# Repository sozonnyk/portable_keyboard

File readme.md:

## DIY Keyboard

This one is WIP

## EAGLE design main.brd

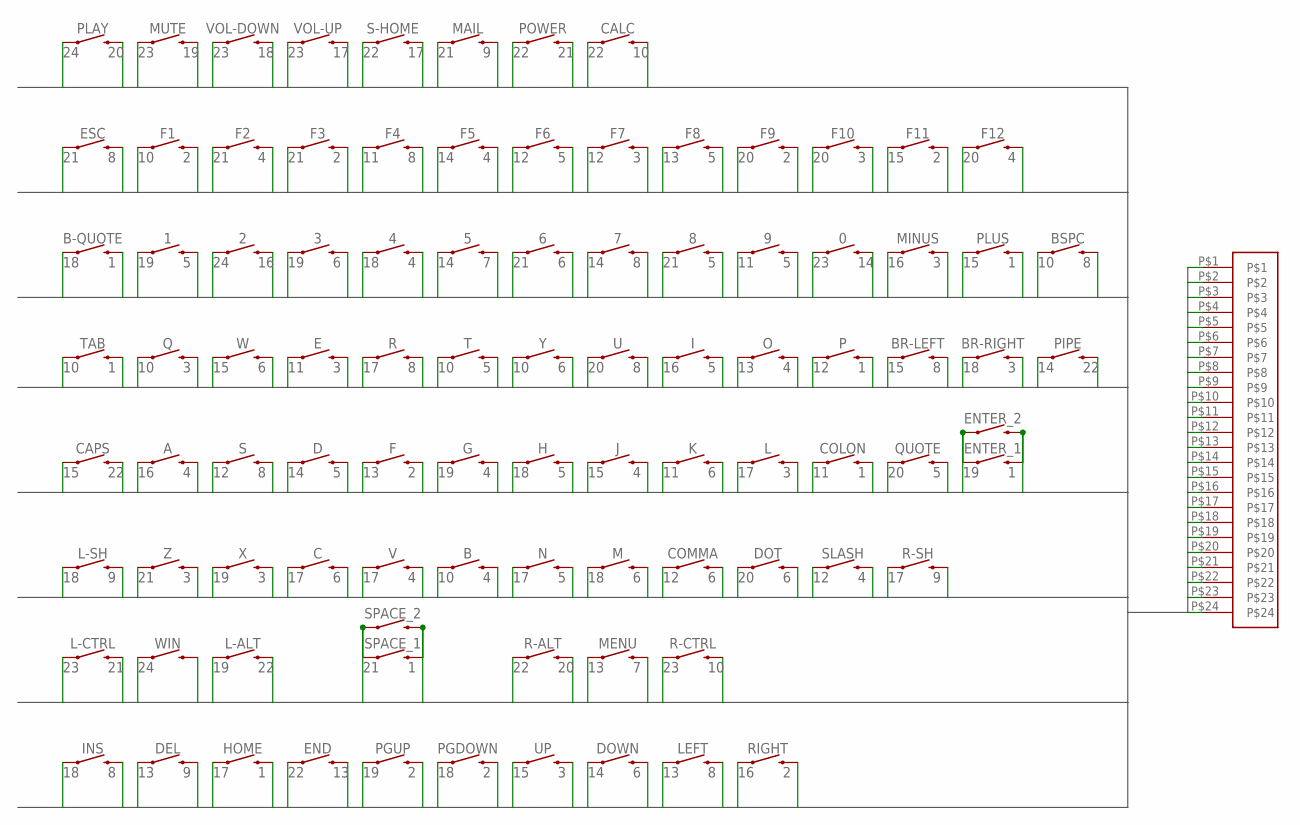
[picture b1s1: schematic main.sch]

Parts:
0, 1, 2, 3, 4, 5, 6, 7, 8, 9: MOMENTARY-SWITCH-SPST-SMD-5.2MM-TALL; TACTILE_SWITCH_SMD_5.2MM
A: MOMENTARY-SWITCH-SPST-SMD-5.2MM-TALL; TACTILE_SWITCH_SMD_5.2MM
B: MOMENTARY-SWITCH-SPST-SMD-5.2MM-TALL; TACTILE_SWITCH_SMD_5.2MM
B-QUOTE: MOMENTARY-SWITCH-SPST-SMD-5.2MM-TALL; TACTILE_SWITCH_SMD_5.2MM
BR-LEFT: MOMENTARY-SWITCH-SPST-SMD-5.2MM-TALL; TACTILE_SWITCH_SMD_5.2MM
BR-RIGHT: MOMENTARY-SWITCH-SPST-SMD-5.2MM-TALL; TACTILE_SWITCH_SMD_5.2MM
BSPC: MOMENTARY-SWITCH-SPST-SMD-5.2MM-TALL; TACTILE_SWITCH_SMD_5.2MM
C: MOMENTARY-SWITCH-SPST-SMD-5.2MM-TALL; TACTILE_SWITCH_SMD_5.2MM
CALC: MOMENTARY-SWITCH-SPST-SMD-5.2MM-TALL; TACTILE_SWITCH_SMD_5.2MM
CAPS: MOMENTARY-SWITCH-SPST-SMD-5.2MM-TALL; TACTILE_SWITCH_SMD_5.2MM
COLON: MOMENTARY-SWITCH-SPST-SMD-5.2MM-TALL; TACTILE_SWITCH_SMD_5.2MM
COMMA: MOMENTARY-SWITCH-SPST-SMD-5.2MM-TALL; TACTILE_SWITCH_SMD_5.2MM
D: MOMENTARY-SWITCH-SPST-SMD-5.2MM-TALL; TACTILE_SWITCH_SMD_5.2MM
DEL: MOMENTARY-SWITCH-SPST-SMD-5.2MM-TALL; TACTILE_SWITCH_SMD_5.2MM
DOT: MOMENTARY-SWITCH-SPST-SMD-5.2MM-TALL; TACTILE_SWITCH_SMD_5.2MM
DOWN: MOMENTARY-SWITCH-SPST-SMD-5.2MM-TALL; TACTILE_SWITCH_SMD_5.2MM
E: MOMENTARY-SWITCH-SPST-SMD-5.2MM-TALL; TACTILE_SWITCH_SMD_5.2MM
END: MOMENTARY-SWITCH-SPST-SMD-5.2MM-TALL; TACTILE_SWITCH_SMD_5.2MM
ENTER_1, ENTER_2: MOMENTARY-SWITCH-SPST-SMD-5.2MM-TALL; TACTILE_SWITCH_SMD_5.2MM
ESC: MOMENTARY-SWITCH-SPST-SMD-5.2MM-TALL; TACTILE_SWITCH_SMD_5.2MM
F, F1, F2, F3, F4, F5, F6, F7, F8, F9, F10, F11, F12: MOMENTARY-SWITCH-SPST-SMD-5.2MM-TALL; TACTILE_SWITCH_SMD_5.2MM
G: MOMENTARY-SWITCH-SPST-SMD-5.2MM-TALL; TACTILE_SWITCH_SMD_5.2MM
H: MOMENTARY-SWITCH-SPST-SMD-5.2MM-TALL; TACTILE_SWITCH_SMD_5.2MM
HOME: MOMENTARY-SWITCH-SPST-SMD-5.2MM-TALL; TACTILE_SWITCH_SMD_5.2MM
I: MOMENTARY-SWITCH-SPST-SMD-5.2MM-TALL; TACTILE_SWITCH_SMD_5.2MM
INS: MOMENTARY-SWITCH-SPST-SMD-5.2MM-TALL; TACTILE_SWITCH_SMD_5.2MM
J: MOMENTARY-SWITCH-SPST-SMD-5.2MM-TALL; TACTILE_SWITCH_SMD_5.2MM
K: MOMENTARY-SWITCH-SPST-SMD-5.2MM-TALL; TACTILE_SWITCH_SMD_5.2MM
L: MOMENTARY-SWITCH-SPST-SMD-5.2MM-TALL; TACTILE_SWITCH_SMD_5.2MM
L-ALT: MOMENTARY-SWITCH-SPST-SMD-5.2MM-TALL; TACTILE_SWITCH_SMD_5.2MM
L-CTRL: MOMENTARY-SWITCH-SPST-SMD-5.2MM-TALL; TACTILE_SWITCH_SMD_5.2MM
L-SH: MOMENTARY-SWITCH-SPST-SMD-5.2MM-TALL; TACTILE_SWITCH_SMD_5.2MM
LEFT: MOMENTARY-SWITCH-SPST-SMD-5.2MM-TALL; TACTILE_SWITCH_SMD_5.2MM
M: MOMENTARY-SWITCH-SPST-SMD-5.2MM-TALL; TACTILE_SWITCH_SMD_5.2MM
MAIL: MOMENTARY-SWITCH-SPST-SMD-5.2MM-TALL; TACTILE_SWITCH_SMD_5.2MM
MENU: MOMENTARY-SWITCH-SPST-SMD-5.2MM-TALL; TACTILE_SWITCH_SMD_5.2MM
MINUS: MOMENTARY-SWITCH-SPST-SMD-5.2MM-TALL; TACTILE_SWITCH_SMD_5.2MM
MUTE: MOMENTARY-SWITCH-SPST-SMD-5.2MM-TALL; TACTILE_SWITCH_SMD_5.2MM
N: MOMENTARY-SWITCH-SPST-SMD-5.2MM-TALL; TACTILE_SWITCH_SMD_5.2MM
O: MOMENTARY-SWITCH-SPST-SMD-5.2MM-TALL; TACTILE_SWITCH_SMD_5.2MM
P: MOMENTARY-SWITCH-SPST-SMD-5.2MM-TALL; TACTILE_SWITCH_SMD_5.2MM
PGDOWN: MOMENTARY-SWITCH-SPST-SMD-5.2MM-TALL; TACTILE_SWITCH_SMD_5.2MM
PGUP: MOMENTARY-SWITCH-SPST-SMD-5.2MM-TALL; TACTILE_SWITCH_SMD_5.2MM
PIPE: MOMENTARY-SWITCH-SPST-SMD-5.2MM-TALL; TACTILE_SWITCH_SMD_5.2MM
PLAY: MOMENTARY-SWITCH-SPST-SMD-5.2MM-TALL; TACTILE_SWITCH_SMD_5.2MM
PLUS: MOMENTARY-SWITCH-SPST-SMD-5.2MM-TALL; TACTILE_SWITCH_SMD_5.2MM
POWER: MOMENTARY-SWITCH-SPST-SMD-5.2MM-TALL; TACTILE_SWITCH_SMD_5.2MM
Q: MOMENTARY-SWITCH-SPST-SMD-5.2MM-TALL; TACTILE_SWITCH_SMD_5.2MM
QUOTE: MOMENTARY-SWITCH-SPST-SMD-5.2MM-TALL; TACTILE_SWITCH_SMD_5.2MM
R: MOMENTARY-SWITCH-SPST-SMD-5.2MM-TALL; TACTILE_SWITCH_SMD_5.2MM
R-ALT: MOMENTARY-SWITCH-SPST-SMD-5.2MM-TALL; TACTILE_SWITCH_SMD_5.2MM
R-CTRL: MOMENTARY-SWITCH-SPST-SMD-5.2MM-TALL; TACTILE_SWITCH_SMD_5.2MM
R-SH: MOMENTARY-SWITCH-SPST-SMD-5.2MM-TALL; TACTILE_SWITCH_SMD_5.2MM
RIGHT: MOMENTARY-SWITCH-SPST-SMD-5.2MM-TALL; TACTILE_SWITCH_SMD_5.2MM
S: MOMENTARY-SWITCH-SPST-SMD-5.2MM-TALL; TACTILE_SWITCH_SMD_5.2MM
S-HOME: MOMENTARY-SWITCH-SPST-SMD-5.2MM-TALL; TACTILE_SWITCH_SMD_5.2MM
SLASH: MOMENTARY-SWITCH-SPST-SMD-5.2MM-TALL; TACTILE_SWITCH_SMD_5.2MM
SPACE_1, SPACE_2: MOMENTARY-SWITCH-SPST-SMD-5.2MM-TALL; TACTILE_SWITCH_SMD_5.2MM
T: MOMENTARY-SWITCH-SPST-SMD-5.2MM-TALL; TACTILE_SWITCH_SMD_5.2MM
TAB: MOMENTARY-SWITCH-SPST-SMD-5.2MM-TALL; TACTILE_SWITCH_SMD_5.2MM
U: MOMENTARY-SWITCH-SPST-SMD-5.2MM-TALL; TACTILE_SWITCH_SMD_5.2MM
U$1: LOGITECH_KBD_24_PIN_CONNECTOR
UP: MOMENTARY-SWITCH-SPST-SMD-5.2MM-TALL; TACTILE_SWITCH_SMD_5.2MM
V: MOMENTARY-SWITCH-SPST-SMD-5.2MM-TALL; TACTILE_SWITCH_SMD_5.2MM
VOL-DOWN: MOMENTARY-SWITCH-SPST-SMD-5.2MM-TALL; TACTILE_SWITCH_SMD_5.2MM
VOL-UP: MOMENTARY-SWITCH-SPST-SMD-5.2MM-TALL; TACTILE_SWITCH_SMD_5.2MM
W: MOMENTARY-SWITCH-SPST-SMD-5.2MM-TALL; TACTILE_SWITCH_SMD_5.2MM
WIN: MOMENTARY-SWITCH-SPST-SMD-5.2MM-TALL; TACTILE_SWITCH_SMD_5.2MM
X: MOMENTARY-SWITCH-SPST-SMD-5.2MM-TALL; TACTILE_SWITCH_SMD_5.2MM
Y: MOMENTARY-SWITCH-SPST-SMD-5.2MM-TALL; TACTILE_SWITCH_SMD_5.2MM
Z: MOMENTARY-SWITCH-SPST-SMD-5.2MM-TALL; TACTILE_SWITCH_SMD_5.2MM

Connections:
1: B-QUOTE.3 (2), COLON.3 (2), ENTER_1.3 (2), ENTER_2.3 (2), HOME.3 (2), P.3 (2), PLUS.3 (2), SPACE_1.3 (2), SPACE_2.3 (2), TAB.3 (2), U$1.P$1
2: F.3 (2), F1.3 (2), F3.3 (2), F9.3 (2), F11.3 (2), PGDOWN.3 (2), PGUP.3 (2), RIGHT.3 (2), U$1.P$2
3: BR-RIGHT.3 (2), E.3 (2), F7.3 (2), F10.3 (2), L.3 (2), MINUS.3 (2), Q.3 (2), U$1.P$3, UP.3 (2), X.3 (2), Z.3 (2)
4: 4.3 (2), A.3 (2), B.3 (2), F2.3 (2), F5.3 (2), F12.3 (2), G.3 (2), J.3 (2), O.3 (2), SLASH.3 (2), U$1.P$4, V.3 (2)
5: 1.3 (2), 8.3 (2), 9.3 (2), D.3 (2), F6.3 (2), F8.3 (2), H.3 (2), I.3 (2), N.3 (2), QUOTE.3 (2), T.3 (2), U$1.P$5
6: 3.3 (2), 6.3 (2), C.3 (2), COMMA.3 (2), DOT.3 (2), DOWN.3 (2), K.3 (2), M.3 (2), U$1.P$6, W.3 (2), Y.3 (2)
7: 5.3 (2), MENU.3 (2), U$1.P$7
8: 7.3 (2), BR-LEFT.3 (2), BSPC.3 (2), ESC.3 (2), F4.3 (2), INS.3 (2), LEFT.3 (2), R.3 (2), S.3 (2), U.3 (2), U$1.P$8
9: DEL.3 (2), L-SH.3 (2), MAIL.3 (2), R-SH.3 (2), U$1.P$9
10: B.1, BSPC.1, CALC.3 (2), F1.1, Q.1, R-CTRL.3 (2), T.1, TAB.1, U$1.P$10, Y.1
11: 9.1, COLON.1, E.1, F4.1, K.1, U$1.P$11, WIN.3 (2)
12: COMMA.1, F6.1, F7.1, P.1, S.1, SLASH.1, U$1.P$12
13: DEL.1, END.3 (2), F.1, F8.1, LEFT.1, MENU.1, O.1, U$1.P$13
14: 0.3 (2), 5.1, 7.1, D.1, DOWN.1, F5.1, PIPE.1, U$1.P$14
15: BR-LEFT.1, CAPS.1, F11.1, J.1, PLUS.1, U$1.P$15, UP.1, W.1
16: 2.3 (2), A.1, I.1, MINUS.1, RIGHT.1, U$1.P$16
17: C.1, HOME.1, L.1, N.1, R.1, R-SH.1, S-HOME.3 (2), U$1.P$17, V.1, VOL-UP.3 (2)
18: 4.1, B-QUOTE.1, BR-RIGHT.1, H.1, INS.1, L-SH.1, M.1, PGDOWN.1, U$1.P$18, VOL-DOWN.3 (2)
19: 1.1, 3.1, ENTER_1.1, ENTER_2.1, G.1, L-ALT.1, MUTE.3 (2), PGUP.1, U$1.P$19, X.1
20: DOT.1, F9.1, F10.1, F12.1, PLAY.3 (2), QUOTE.1, R-ALT.3 (2), U.1, U$1.P$20
21: 6.1, 8.1, ESC.1, F2.1, F3.1, L-CTRL.3 (2), MAIL.1, POWER.3 (2), SPACE_1.1, SPACE_2.1, U$1.P$21, Z.1
22: CALC.1, CAPS.3 (2), END.1, L-ALT.3 (2), PIPE.3 (2), POWER.1, R-ALT.1, S-HOME.1, U$1.P$22
23: 0.1, L-CTRL.1, MUTE.1, R-CTRL.1, U$1.P$23, VOL-DOWN.1, VOL-UP.1
24: 2.1, PLAY.1, U$1.P$24, WIN.1

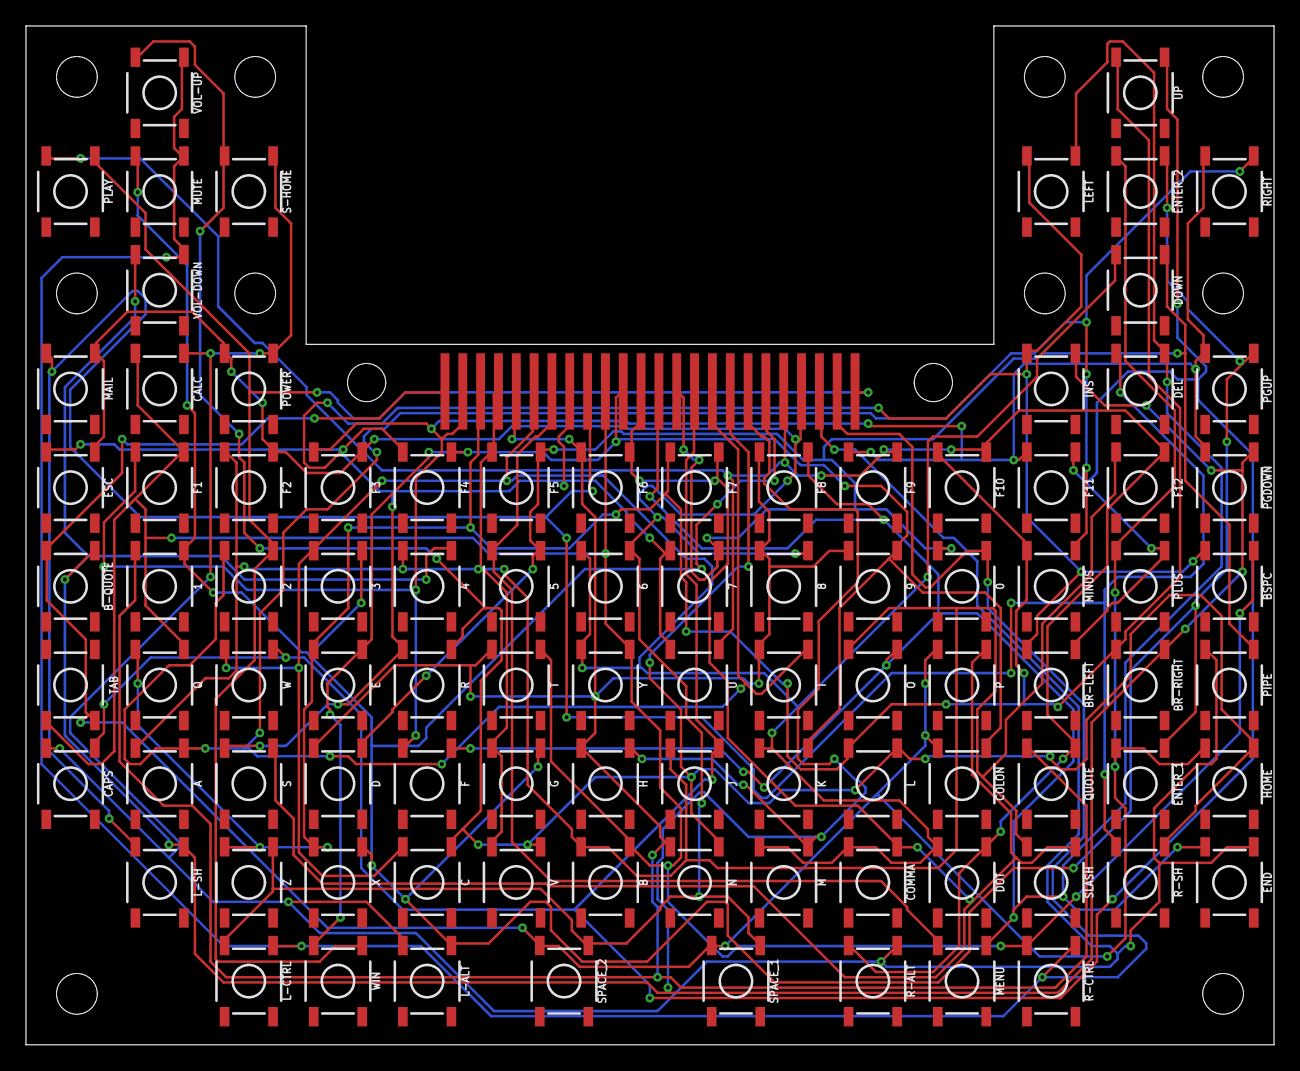
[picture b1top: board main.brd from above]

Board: 2 copper layers, 98.0 x 80.0 mm, 94 parts (0 on the bottom side), 24 nets.

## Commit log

2019-04-08 Fixing images
2019-04-11 Adding layout table
2019-11-25 More pictures
2019-11-25 Lost images
2019-12-04 Adding scale picture

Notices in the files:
parts and their libraries:
SparkFun-Switches: Licensing: Creative Commons ShareAlike 4.0 International - https://creativecommons.org/licenses/by-sa/4.0
